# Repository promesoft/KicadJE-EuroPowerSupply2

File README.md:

# KicadJE-EuroPowerSupply2
4HP PSU faceplate with 80x100mm PSU + PDU board. Faceplate input from a laptop PSU (19V) and may be daisychained to the next Eurorack unit.

Please note this method of making +- 12v could be impaired by the laptop PSU ground connection. Some PSU's connect earth to GND (sleeve) which will be connected to -12v and not GND in this circuit. If the laptop PSU only has 2 pins or the 3rd pin is not connected to the sleeve of 19v supply there will be no issues with this design.

There is a third version that does not rely on a laptop supply in the making (2025 Q1)

# Vital Components

# Status - mounted in rack
## Initial 
| Stage  | Detail | Status |
| ------------- | ------------- | ------------- |
| create material  | sch | done |
| | pcb | done |
| | gerber | done |
| production  |   | done |
|  | produced | done |
|  | delivered | done |
## Preliminary validation
| Test  | Detail | Status |
| ------------- | ------------- | ------------- |
| Initial Inspection | | good alignment w panel - panel: pwr holes 2 mm too small |
| Initial Technical Test |  | OL LED's lighting up without load - probably due to the extra resistance of the polyfuse |
| Initial Technical Test |  | OL LED's ok with 2k2 but unsure of how they work now - 3k9 is ok without load but makes a bit of a light at a few XX mA |
| Initial Technical Test |  | input fuse experienced a few problems after shoring the input of the DC-DC by mistake
| Initial Product Test |  | ok - Powers the uP DAC nicely|

## Secondary validation
| Test  | Detail | Status |
| ------------- | ------------- |------------- |
| Product Test |  | |
| Product Test |  | |
| Quality |  | |
| Quality | | |
| Long Term Product Test |  | Working for a year without stability issues | 
|  | | Bridge recitifier gets warm/hot |
| Power Draw | up to 750mA 19V | 

## Errata
### Errata - 
Holes for Pwr in and out are 2mm too small in face plate

Place DCDC input further away from electronics on the backside - risky location

## Issues and Notes
### Front
There is just enough room on the front PCB to add a JST header for power feed to baseboard.

### Regulation
Input cap C101 = 470uF/50V

Reg input cap C207 - 470uF/16V for 5V

Reg input cap C204 C212 - 100uF/35V for +-12V

Reg output cap C206 C209 C214 - 470uF/16V for all

### Output
Only half the headers has decoupling caps

Place +/-15v header away from heatsink area.

### Overload Circuit
Not easy to measure the OL circuit as it is VERY close to the DC-DC input  
Add current limiter on input and consider changing from OL to currentlimier with limit indication  
OL LED's ok with 2k2 but unsure of how they work now - 3k9 is ok without load but makes a bit of a light at a few XX mA  

### Extensions
Consider calc initial regulator stage as Capacitor multiplier and add small signal BJT in darlington config.
 - https://www.google.com/search?q=eeblog+david+jones+capacitor+multiplier&oq=eeblog+david+jones+capacitor+mul&aqs=chrome.1.69i57j33.18679j1j7&sourceid=chrome&ie=UTF-8

# Pictures

## Rendered

# Schematic

## Prototype

# Inspiration
## Rev 1
https://github.com/promesoft/KicadJE-EuroPowerSupply

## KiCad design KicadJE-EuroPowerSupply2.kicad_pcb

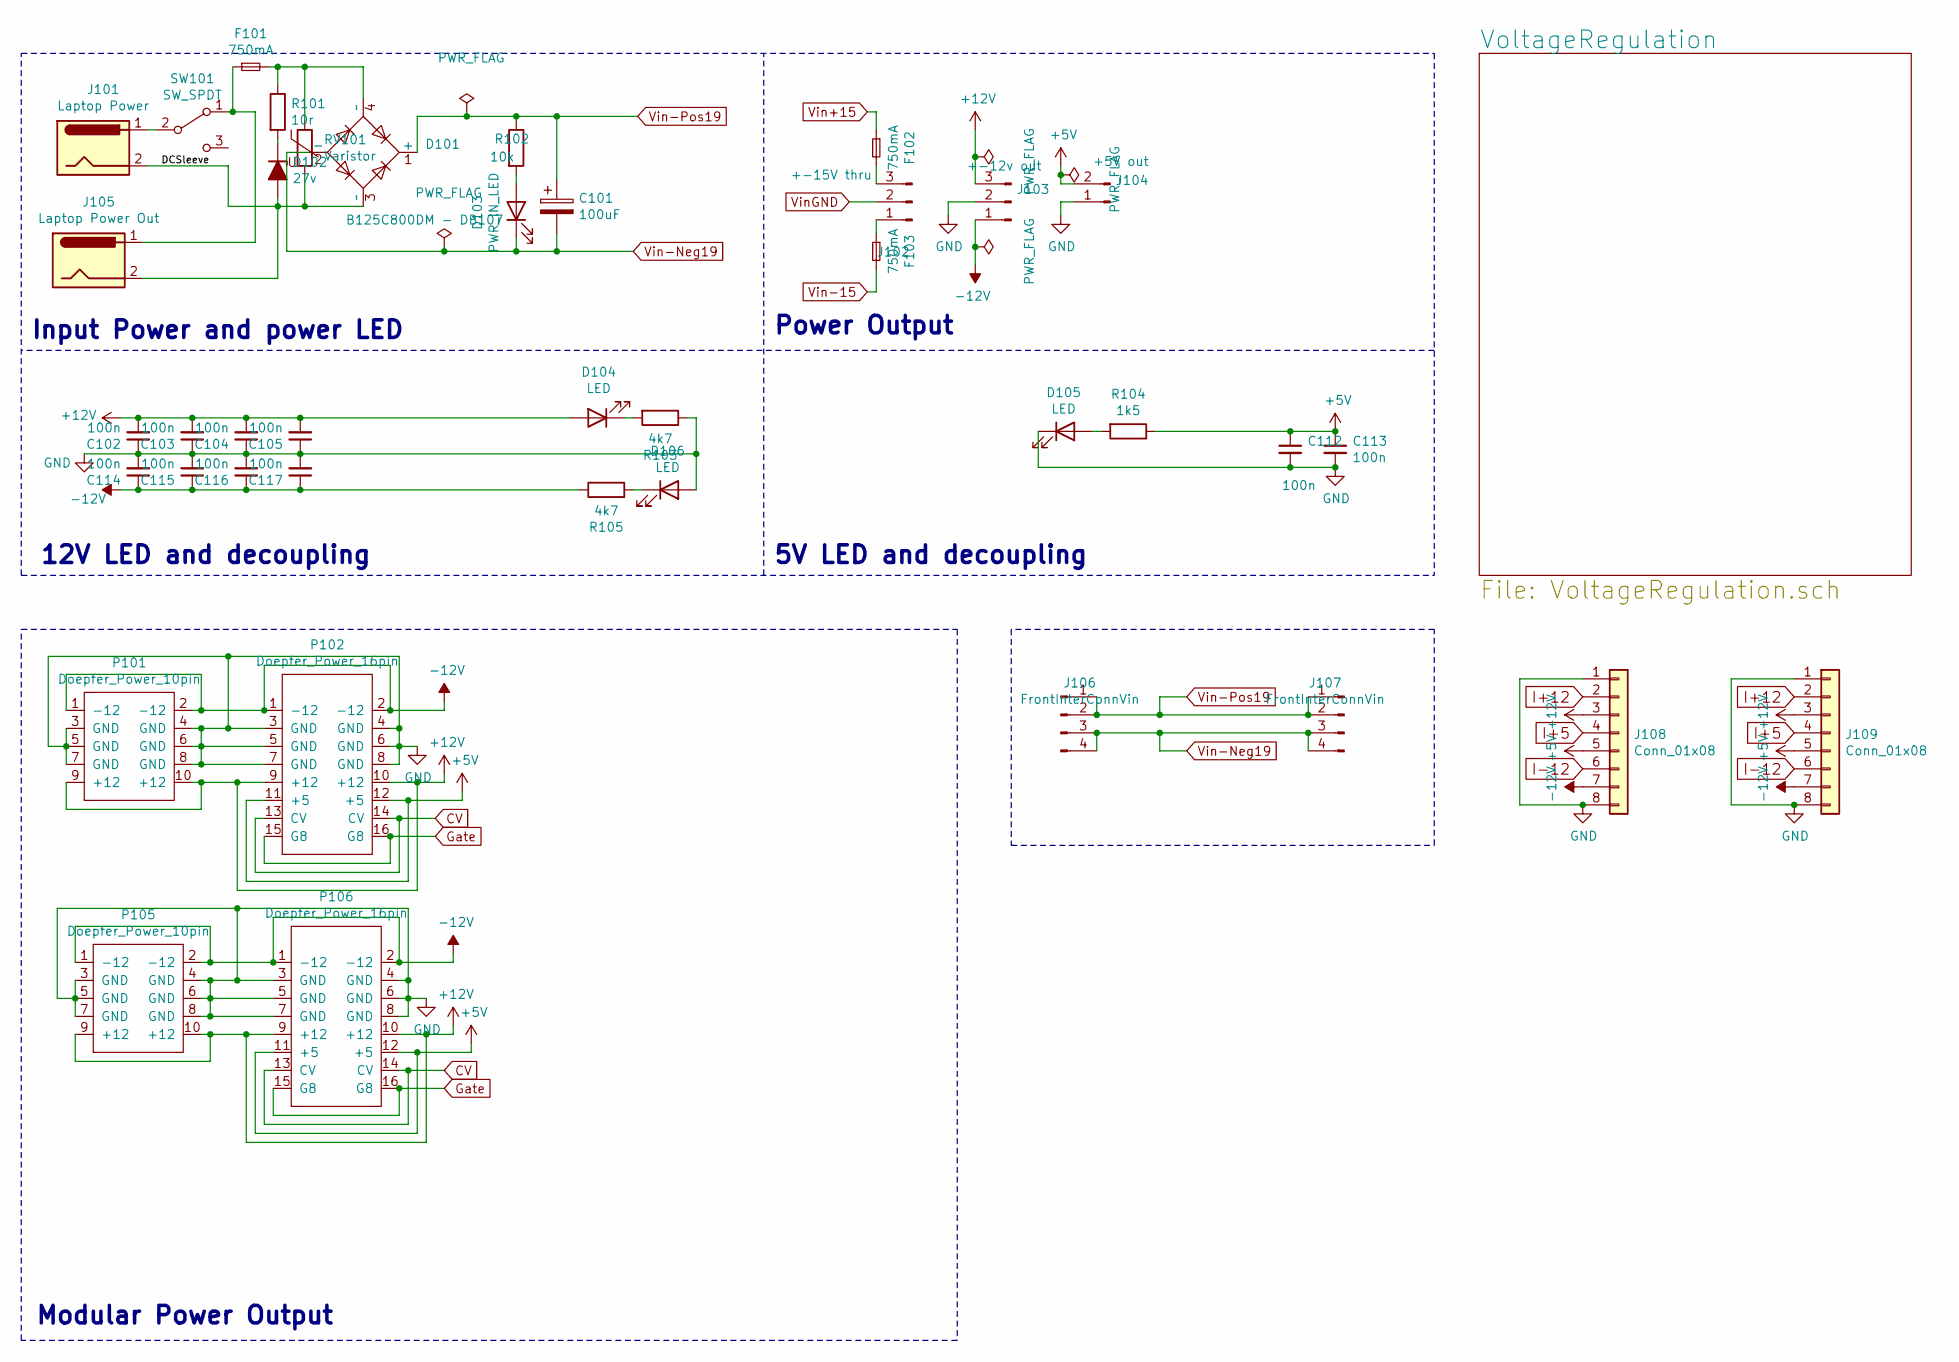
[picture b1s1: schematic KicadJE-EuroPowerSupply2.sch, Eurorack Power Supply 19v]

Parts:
C101: 100uF; CP_Radial_D10.0mm_P5.00mm
C102, C103, C104, C105, C112, C113, C114, C115, C116, C117: 100n; C_0805_2012Metric_Pad1.15x1.40mm_HandSolder
D101: B125C800DM - DB107; Diode_Bridge_DIP-4_W7.62mm_P5.08mm
D102: 27v; D_MiniMELF_Handsoldering
D103: PWR_IN_LED; LED_D5.0mm
D104, D105, D106: LED; LED_D5.0mm
F101, F102, F103: 750mA; Fuse_1812_4532Metric_Pad1.30x3.40mm_HandSolder
J101: Laptop Power; BarrelJack_CUI_PJ-063AH_Horizontal
J102: +-15V thru; TerminalBlock_Altech_AK300-3_P5.00mm
J103: +-12v out; TerminalBlock_Altech_AK300-3_P5.00mm
J104: +5V out; TerminalBlock_Altech_AK300-2_P5.00mm
J105: Laptop Power Out; BarrelJack_CUI_PJ-063AH_Horizontal
J106, J107: FrontInterConnVin; PinHeader_1x04_P2.54mm_Vertical
J108, J109: Conn_01x08; PinHeader_1x08_P2.54mm_Vertical
P101, P105: Doepfer_Power_10pin; IDC-Header_2x05_Pitch2.54mm_Straight
P102, P106: Doepfer_Power_16pin; IDC-Header_2x08_Pitch2.54mm_Straight
R101: 10r; R_0805_2012Metric_Pad1.15x1.40mm_HandSolder
R102: 10k; R_0805_2012Metric_Pad1.15x1.40mm_HandSolder
R103, R105: 4k7; R_0805_2012Metric_Pad1.15x1.40mm_HandSolder
R104: 1k5; R_0805_2012Metric_Pad1.15x1.40mm_HandSolder
RV101: Varistor; RV_Disc_D12mm_W4.8mm_P7.5mm
SW101: SW_SPDT; SP1MS1

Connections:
+5V: C112.1, C113.1, J104.2, J108.5, J109.5, P102.11 (+5), P102.12 (+5), P106.11 (+5), P106.12 (+5), R104.1; also elsewhere on the board
+12V: C102.2, C103.2, C104.2, C105.2, D104.2 (A), J103.3, J108.3, J109.3, P101.9 (+12), P101.10 (+12), P102.9 (+12), P102.10 (+12), P105.9 (+12), P105.10 (+12), P106.9 (+12), P106.10 (+12); also elsewhere on the board
-12V: C114.1, C115.1, C116.1, C117.1, J103.1, J108.7, J109.7, P101.1 (-12), P101.2 (-12), P102.1 (-12), P102.2 (-12), P105.1 (-12), P105.2 (-12), P106.1 (-12), P106.2 (-12), R105.1; also elsewhere on the board
/DCSleeve: D101.3 (~~), D102.2 (A), J101.2, J105.2, RV101.2
CV: P102.13 (CV), P102.14 (CV), P106.13 (CV), P106.14 (CV)
GND: C102.1, C103.1, C104.1, C105.1, C112.2, C113.2, C114.2, C115.2, C116.2, C117.2, D105.1 (K), D106.2 (A), J103.2, J104.1, J108.1, J108.8, J109.1, J109.8, P101.3 (GND), P101.4 (GND), P101.5 (GND), P101.6 (GND), P101.7 (GND), P101.8 (GND), P102.3 (GND), P102.4 (GND), P102.5 (GND), P102.6 (GND), P102.7 (GND), P102.8 (GND), P105.3 (GND), P105.4 (GND), P105.5 (GND), P105.6 (GND), P105.7 (GND), P105.8 (GND), P106.3 (GND), P106.4 (GND), P106.5 (GND), P106.6 (GND), P106.7 (GND), P106.8 (GND), R103.1; also elsewhere on the board
Gate: P102.15 (G8), P102.16 (G8), P106.15 (G8), P106.16 (G8)
I+5: J108.4, J109.4; also elsewhere on the board
I+12: J108.2, J109.2; also elsewhere on the board
I-12: J108.6, J109.6; also elsewhere on the board
unnamed: D101.4 (~~), F101.2, R101.1, RV101.1
unnamed: D102.1 (K), R101.2
unnamed: D103.2 (A), R102.2
unnamed: D104.1 (K), R103.2
unnamed: D105.2 (A), R104.2
unnamed: D106.1 (K), R105.2
unnamed: F101.1, J105.1, SW101.1 (A)
unnamed: F102.2, J102.3
unnamed: F103.1, J102.1
unnamed: J101.1, SW101.2 (B)
Vin+15: F102.1; also elsewhere on the board
Vin-15: F103.2; also elsewhere on the board
Vin-Neg19: C101.2, D101.2 (-), D103.1 (K), J106.3, J106.4, J107.3, J107.4; also elsewhere on the board
Vin-Pos19: C101.1, D101.1 (+), J106.1, J106.2, J107.1, J107.2, R102.1; also elsewhere on the board
VinGND: J102.2; also elsewhere on the board

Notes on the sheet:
12V LED and decoupling
Modular Power Output
5V LED and decoupling
Input Power and power LED
Power Output

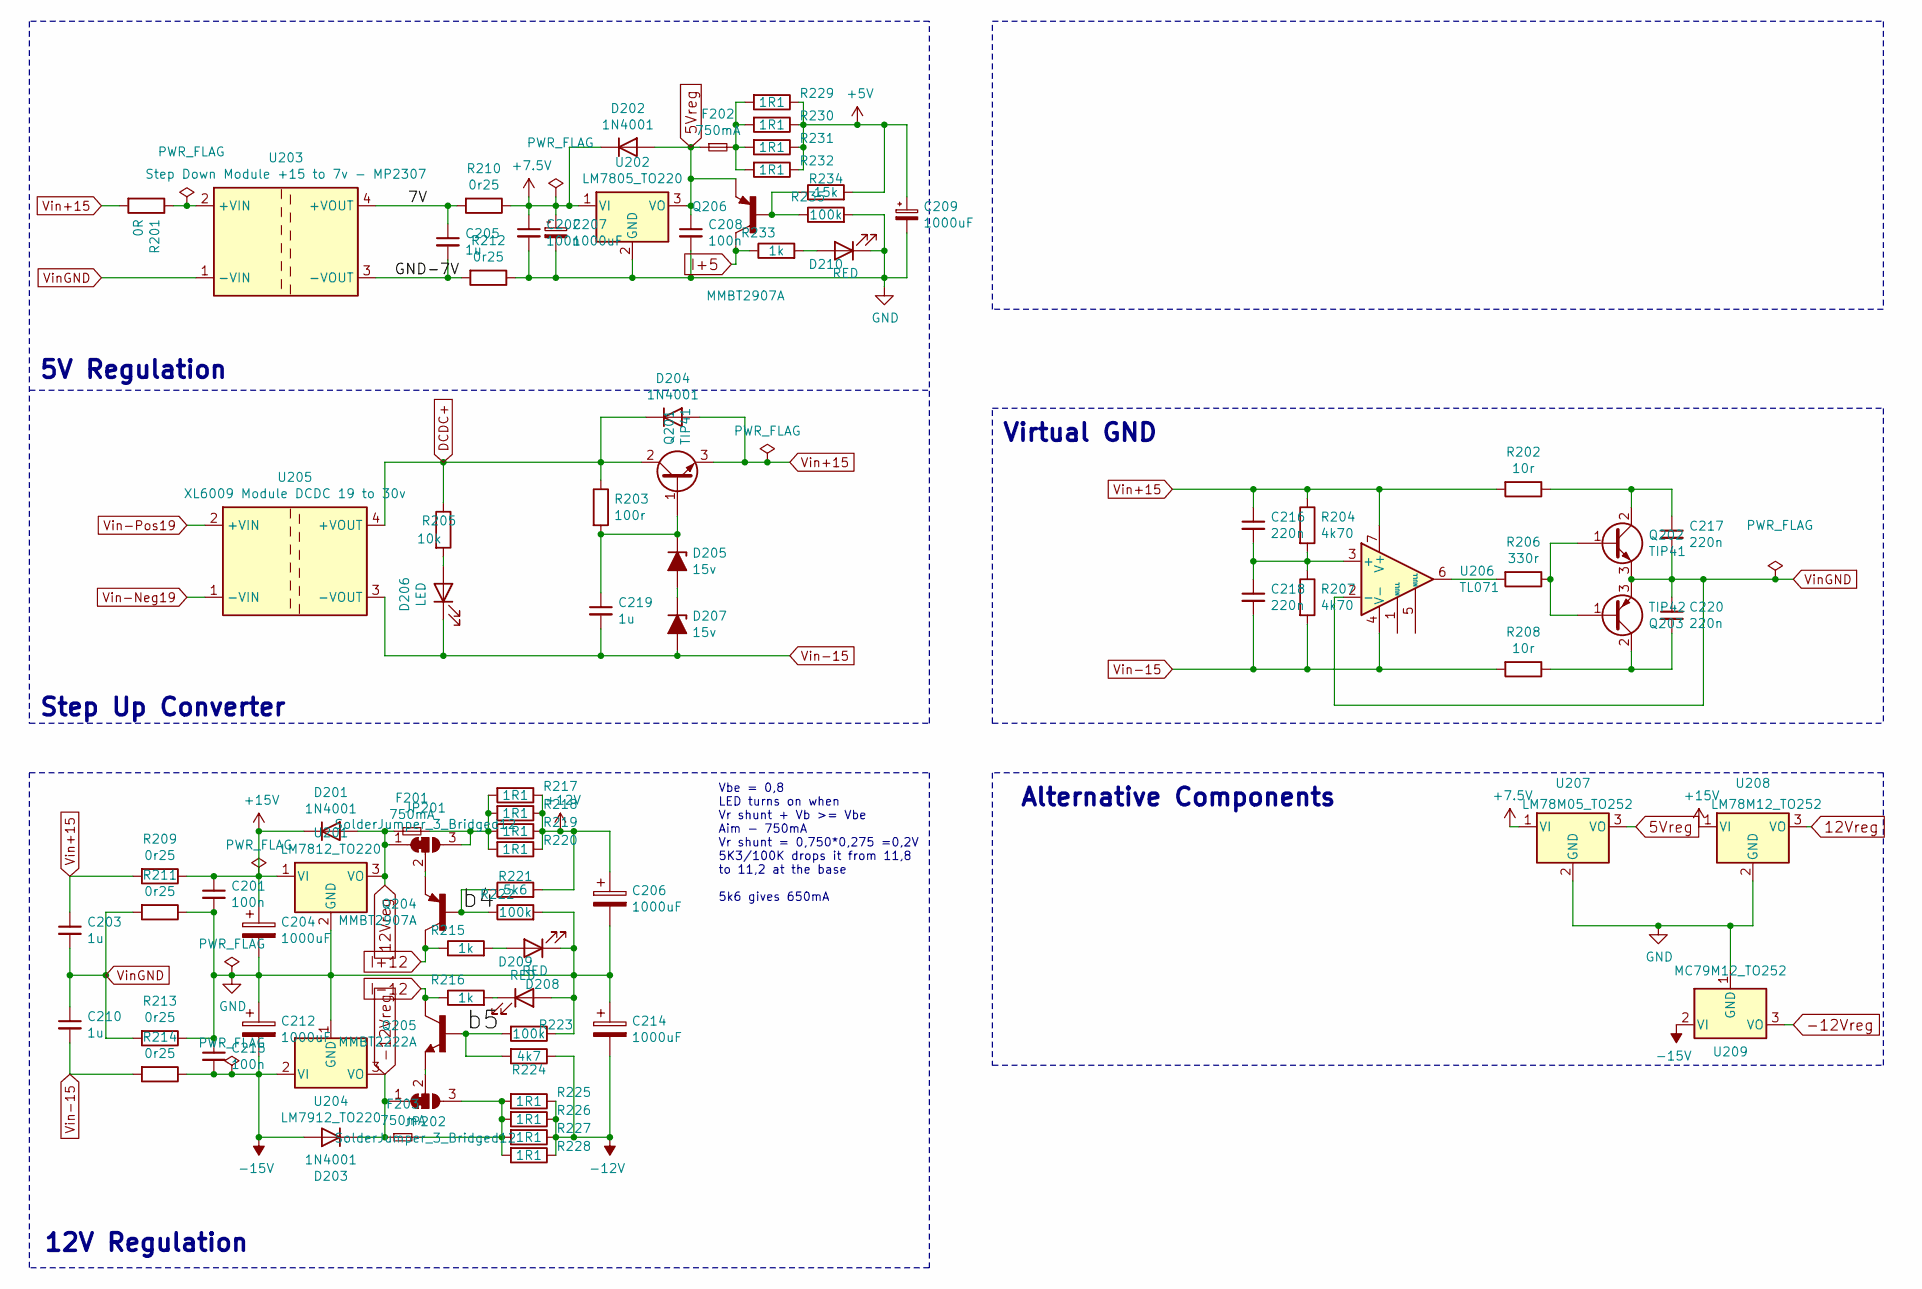
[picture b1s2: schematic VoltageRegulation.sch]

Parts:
C201, C202, C208, C215: 100n; C_0805_2012Metric_Pad1.15x1.40mm_HandSolder
C203, C205, C210, C219: 1u; C_1206_3216Metric_Pad1.42x1.75mm_HandSolder
C204, C207, C212: 1000uF; CP_Radial_D8.0mm_P3.80mm
C206, C209, C214: 1000uF; CP_Radial_D10.0mm_P5.00mm
C216, C217, C218, C220: 220n; C_0805_2012Metric_Pad1.15x1.40mm_HandSolder
D201, D202, D203, D204: 1N4001; D_SOD-123
D205, D207: 15v; D_MiniMELF
D206: LED; LED_0805_2012Metric_Pad1.15x1.40mm_HandSolder
D208, D209, D210: RED; LED_D5.0mm
F201, F202, F203: 750mA; Fuse_1210_3225Metric_Pad1.42x2.65mm_HandSolder
JP201, JP202: SolderJumper_3_Bridged12; SolderJumper-3_P1.3mm_Bridged12_RoundedPad1.0x1.5mm_NumberL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
Q201, Q202: TIP41; TO-220-3_Vertical
Q203: TIP42; TO-220-3_Vertical
Q204, Q206: MMBT2907A; SOT-23_Handsoldering
Q205: MMBT2222A; SOT-23_Handsoldering
R201: 0R; R_0805_2012Metric_Pad1.15x1.40mm_HandSolder
R202, R208: 10r; R_Axial_DIN0204_L3.6mm_D1.6mm_P2.54mm_Vertical
R203: 100r; R_0805_2012Metric_Pad1.15x1.40mm_HandSolder
R204, R207: 4k70; R_0805_2012Metric_Pad1.15x1.40mm_HandSolder
R205: 10k; R_0805_2012Metric_Pad1.15x1.40mm_HandSolder
R206: 330r; R_0805_2012Metric_Pad1.15x1.40mm_HandSolder
R209, R210, R211, R212, R213, R214: 0r25; R_Axial_DIN0204_L3.6mm_D1.6mm_P5.08mm_Vertical
R215, R216, R233: 1k; R_0805_2012Metric_Pad1.15x1.40mm_HandSolder
R217, R218, R219, R220, R225, R226, R227, R228, R229, R230, R231, R232: 1R1; R_0805_2012Metric_Pad1.15x1.40mm_HandSolder
R221: 5k6; R_0805_2012Metric_Pad1.15x1.40mm_HandSolder
R222, R223, R235: 100k; R_0805_2012Metric_Pad1.15x1.40mm_HandSolder
R224: 4k7; R_0805_2012Metric_Pad1.15x1.40mm_HandSolder
R234: 15k; R_0805_2012Metric_Pad1.15x1.40mm_HandSolder
U201: LM7812_TO220; TO-220-3_Vertical
U202: LM7805_TO220; TO-220-3_Vertical
U203: Step Down Module +15 to 7v - MP2307; MP2307 DCDC module
U204: LM7912_TO220; TO-220-3_Vertical
U205: XL6009 Module DCDC 19 to 30v; XL6009-DCDC-Module
U206: TL071; DIP-8_W7.62mm_Socket
U207: LM78M05_TO252; TO-252-3_TabPin2
U208: LM78M12_TO252; TO-252-3_TabPin2
U209: MC79M12_TO252; TO-252-3_TabPin2

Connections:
5Vreg: C208.1, D202.2 (A), F202.1, Q206.2 (E), U202.3 (VO), U207.3 (VO)
12Vreg: D201.2 (A), F201.1, JP201.1 (A), U201.3 (VO), U208.3 (VO)
+5V: C209.1, R229.1, R230.1, R231.1, R232.1, R234.2; also elsewhere on the board
+7.5V: C202.1, C207.1, D202.1 (K), R210.1, U202.1 (VI), U207.1 (VI)
+12V: C206.1, R217.1, R218.1, R219.1, R220.1, R221.2; also elsewhere on the board
+15V: C201.1, C204.1, D201.1 (K), R209.1, U201.1 (VI), U208.1 (VI)
-12V: C214.2, R224.1, R225.1, R226.1, R227.1, R228.1; also elsewhere on the board
-12Vreg: D203.1 (K), F203.1, JP202.1 (A), U204.3 (VO), U209.3 (VO)
-15V: C212.2, C215.2, D203.2 (A), R214.1, U204.2 (VI), U209.2 (VI)
/VoltageRegulation/7V: C205.1, R210.2, U203.4 (+VOUT)
/VoltageRegulation/GND-7V: C205.2, R212.2, U203.3 (-VOUT)
/VoltageRegulation/b4: Q204.1 (B), R221.1, R222.1
/VoltageRegulation/b5: Q205.1 (B), R223.2, R224.2
DCDC+: D204.1 (K), Q201.2 (C), R203.1, R205.1, U205.4 (+VOUT)
GND: C201.2, C202.2, C204.2, C206.2, C207.2, C208.2, C209.2, C212.1, C214.1, C215.1, D208.2 (A), D209.1 (K), D210.1 (K), R211.1, R212.1, R213.1, R222.2, R223.1, R235.2, U201.2 (GND), U202.2 (GND), U204.1 (GND), U207.2 (GND), U208.2 (GND), U209.1 (GND); also elsewhere on the board
I+5: Q206.3 (C), R233.1; also elsewhere on the board
I+12: Q204.3 (C), R215.1; also elsewhere on the board
I-12: Q205.3 (C), R216.1; also elsewhere on the board
unnamed: C216.2, C218.1, R204.2, R207.1, U206.3 (+)
unnamed: C217.1, Q202.2 (C), R202.1
unnamed: C219.1, D205.1 (K), Q201.1 (B), R203.2
unnamed: C220.2, Q203.2 (C), R208.1
unnamed: D205.2 (A), D207.1 (K)
unnamed: D206.2 (A), R205.2
unnamed: D208.1 (K), R216.2
unnamed: D209.2 (A), R215.2
unnamed: D210.2 (A), R233.2
unnamed: F201.2, JP201.3 (B), R217.2, R218.2, R219.2, R220.2
unnamed: F202.2, R229.2, R230.2, R231.2, R232.2
unnamed: F203.2, JP202.3 (B), R225.2, R226.2, R227.2, R228.2
unnamed: JP201.2 (C), Q204.2 (E)
unnamed: JP202.2 (C), Q205.2 (E)
unnamed: Q202.1 (B), Q203.1 (B), R206.1
unnamed: Q206.1 (B), R234.1, R235.1
unnamed: R201.1, U203.2 (+VIN)
unnamed: R206.2, U206.6
Vin+15: C203.1, C216.1, D204.2 (A), Q201.3 (E), R201.2, R202.2, R204.1, R209.2, U206.7 (V+); also elsewhere on the board
Vin-15: C210.2, C218.2, C219.2, D206.1 (K), D207.2 (A), R207.2, R208.2, R214.2, U205.3 (-VOUT), U206.4 (V-); also elsewhere on the board
Vin-Neg19: U205.1 (-VIN); also elsewhere on the board
Vin-Pos19: U205.2 (+VIN); also elsewhere on the board
VinGND: C203.2, C210.1, C217.2, C220.1, Q202.3 (E), Q203.3 (E), R211.2, R213.2, U203.1 (-VIN), U206.2 (-); also elsewhere on the board

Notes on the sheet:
12V Regulation
Alternative Components
5V Regulation
Step Up Converter
Virtual GND
Vbe = 0,8 LED turns on when Vr shunt + Vb >= Vbe Aim - 750mA Vr shunt = 0,750*0,275 =0,2V 5K3/100K drops it from 11,8 to 11,2 at the base 5k6 gives 650mA

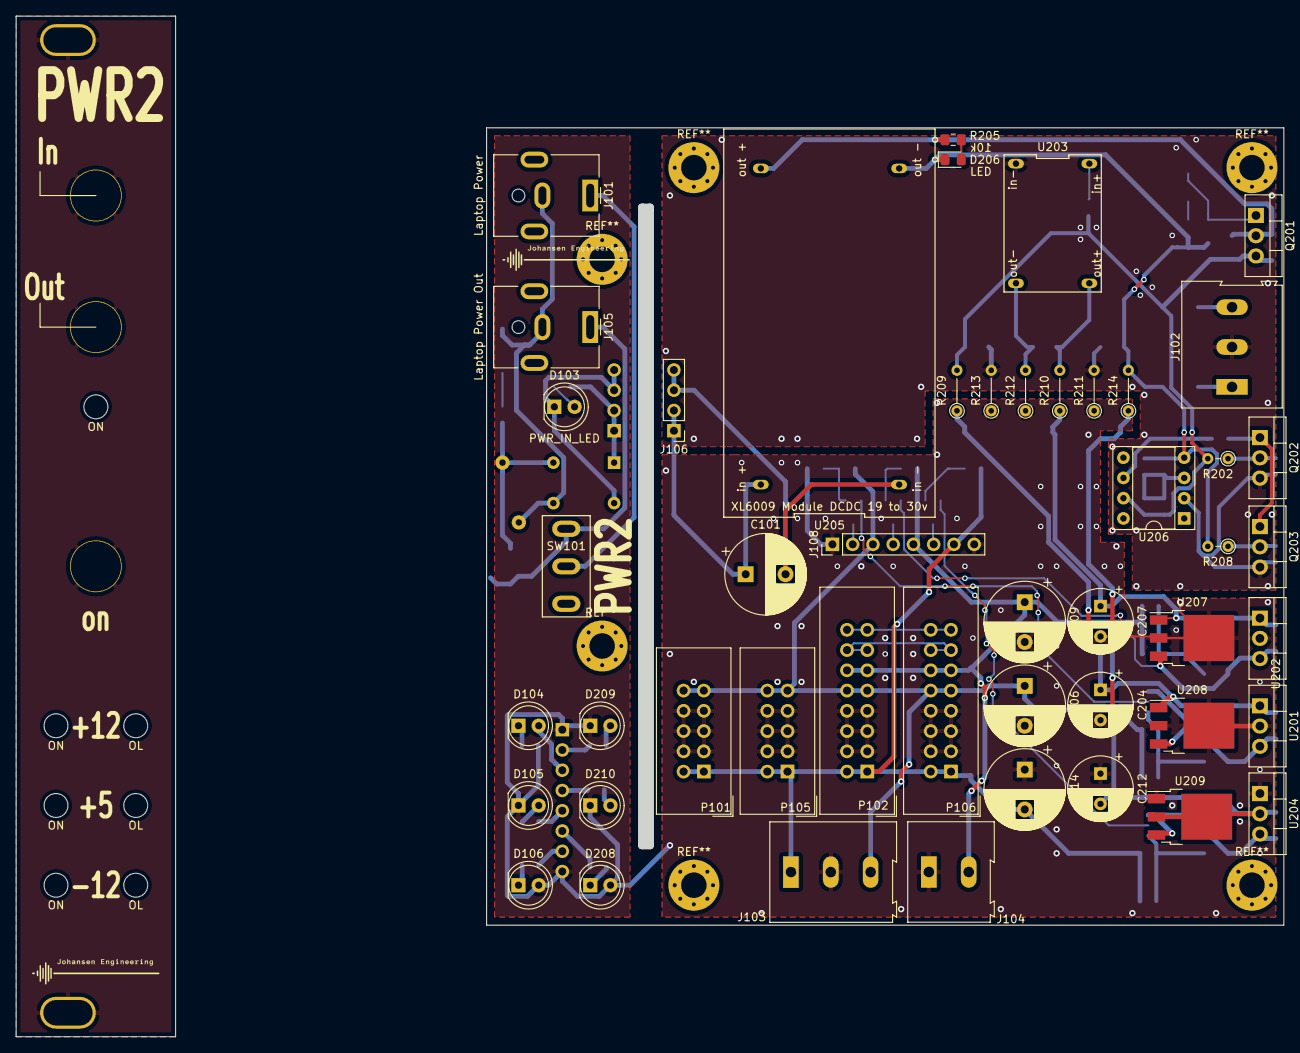
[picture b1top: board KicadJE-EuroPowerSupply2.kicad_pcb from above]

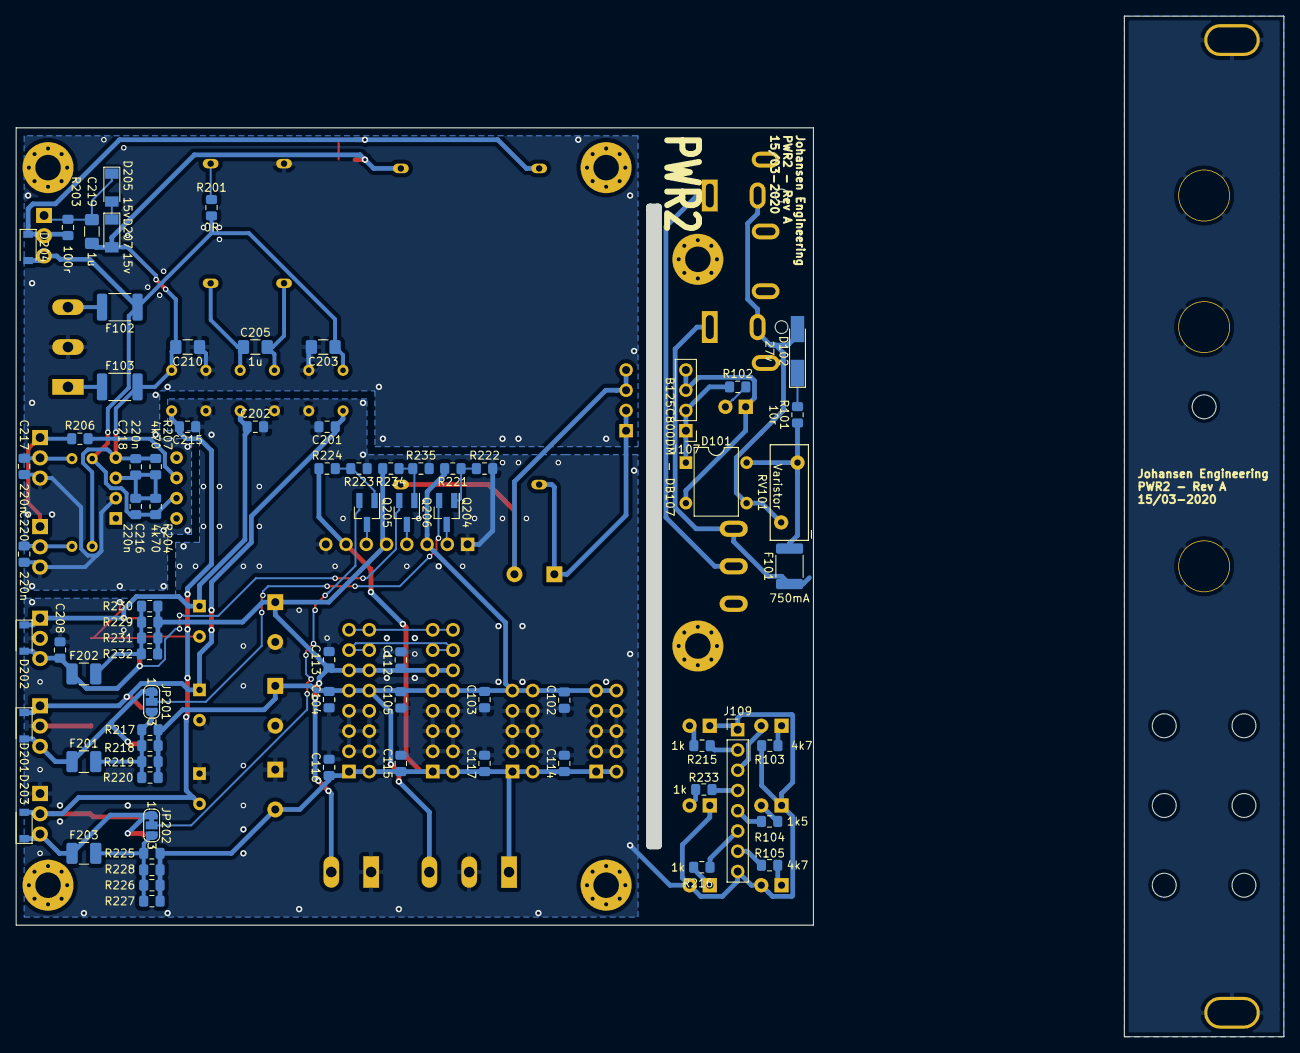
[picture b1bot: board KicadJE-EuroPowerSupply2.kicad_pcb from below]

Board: 2 copper layers, 100.0 x 100.0 mm, 135 parts (76 on the bottom side), 54 nets.

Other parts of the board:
H101, H102: MountingHole_Pad; MountingHole_Eurorack3
H105, H105#3, H105#5: OL; LED_Hole_3mm
H105#2, H105#4, H105#6, H105#7: ON; LED_Hole_3mm
TP109: Tri; Jack_6m3
TP110, TP110#2: SQ; Jack_6m3

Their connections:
GND: H101.1, H102.1, TP109.1, TP110.1, TP110#2.1; also elsewhere on the board

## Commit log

2020-03-12 init from old projects
2020-03-15 Init 750mA indicator
2020-03-15 5V current sensor
2020-03-15 Jumper before/after fuse
2020-03-15 placing first components
2020-03-15 Faceplate
2020-03-15 interboard connector
2020-03-15 PCB adjustments
2020-03-15 Almost completely placed
2020-03-16 Update KicadJE-EuroPowerSupply2.kicad_pcb
    Components placed
2020-03-16 Board setup - power lines
2020-03-16 Images
2020-03-16 Update KicadJE-EuroPowerSupply2.kicad_pcb
    Wired initially
2020-03-17 Update KicadJE-EuroPowerSupply2.kicad_pcb
    DRC + Labels
2020-03-17 Complete Gerber Rev A
2020-03-17 Faceplate Gerber
2020-03-17 PCB Gerber
    Gerber
2020-03-17 Gerber update
2020-04-21 sch png
2020-04-27 version upd
2021-04-22 Update Kicad version
2025-01-16 Update README.md
    Please note this method of making +- 12v could be impaired by the laptop PSU ground connection. Some PSU's connect earth to GND (sleeve) which will be connected to -12v and not GND in this circuit.
2025-02-04 Update README.md
    Schematic on readme
2025-02-05 Real life pictures
2025-02-05 remove spaces
2025-02-05 Inside_pic
